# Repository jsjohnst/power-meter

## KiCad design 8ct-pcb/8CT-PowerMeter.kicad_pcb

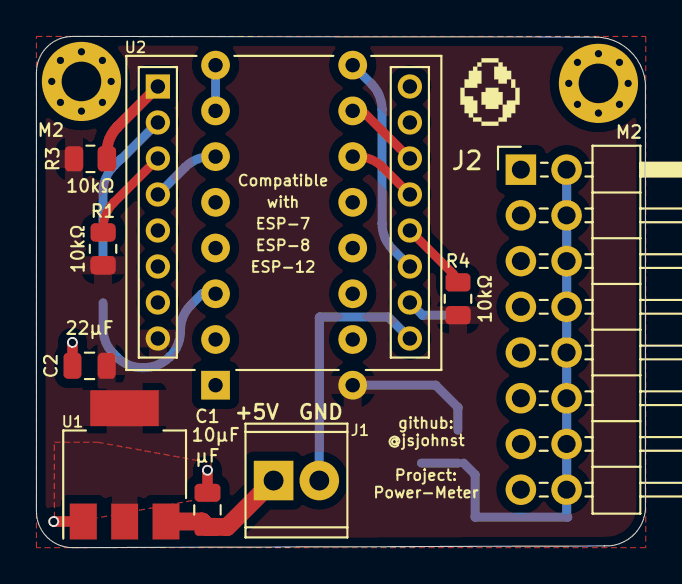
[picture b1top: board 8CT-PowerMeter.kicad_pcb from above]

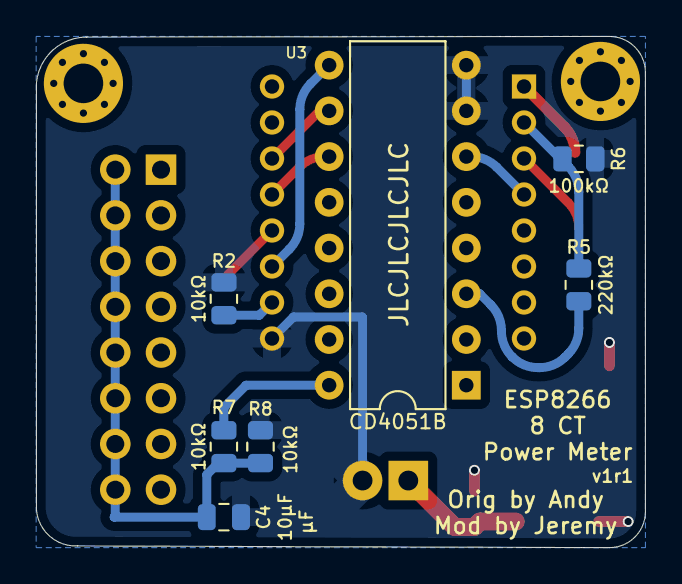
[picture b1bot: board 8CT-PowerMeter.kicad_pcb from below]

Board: 4 copper layers, 33.8 x 28.4 mm, 18 parts (7 on the bottom side), 22 nets.

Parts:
C1, C4: 10µF; C_0805_2012Metric
C2: 22µF; C_0805_2012Metric
H1, H2: M2; MountingHole_2.2mm_M2_Pad_Via
J1: Screw_Terminal_01x02; TerminalBlock_Phoenix_MPT-0,5-2-2.54_1x02_P2.54mm_Horizonta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
J2: Conn_02x08_Odd_Even; PinHeader_2x08_P2.54mm_Horizontal
R1, R2, R3, R4, R7, R8: 10kΩ; R_0805_2012Metric
R5: 220kΩ; R_0805_2012Metric
R6: 100kΩ; R_0805_2012Metric
U1: AMS1117-3.3; SOT-223-3_TabPin2
U2: ESP-07; ESP-12-Socket-Cutout
U3: CD4051B; DIP-16_W7.62mm

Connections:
+3V3: C2.1, R1.1, R3.1, R4.1, R7.1, U1.2 (VO), U2.8 (VCC), U3.16 (VDD)
/+5V: C1.1, J1.1, U1.3 (VI)
/ADCRAW: R5.1, U3.3 (X)
A0: R5.2, R6.1, U2.2 (ADC)
GND: C1.2, C2.2, C4.1, J1.2, R2.2, R6.2, R8.2, U1.1 (GND), U2.15 (GND), U3.7 (VEE), U3.8 (VSS)
GPIO2: U2.17 (GPIO2), U3.9 (C)
GPIO4: U2.19 (GPIO4), U3.11 (A)
GPIO5: U2.20 (GPIO5), U3.10 (B)
GPIO16: U2.4 (GPIO16), U3.6 (INH)
unnamed: C4.2, J2.2, J2.4, J2.6, J2.8, J2.10, J2.12, J2.14, J2.16, R7.2, R8.1
unnamed: R1.2, U2.3 (EN)
unnamed: R2.1, U2.16 (GPIO15)
unnamed: R3.2, U2.1 (~RST)
unnamed: R4.2, U2.18 (GPIO0)
PM1: J2.1, U3.13 (X0)
PM2: J2.3, U3.14 (X1)
PM3: J2.5, U3.15 (X2)
PM4: J2.7, U3.12 (X3)
PM5: J2.15, U3.1 (X4)
PM6: J2.9, U3.5 (X5)
PM7: J2.13, U3.2 (X6)
PM8: J2.11, U3.4 (X7)

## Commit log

2023-01-01 Adding new 8 channel version of Power Meter
    As the mux is 8 channels, why limit ourselves to just 3 CTs? :) To keep
    the small footprint of the original board design as close as possible,
    the board was increased from 2 layers to 4 layers. The signal lines
    going from the mux to the CT pin header uses the inner two layers of the
    board design.
    This new design passes KiCad validation checks, but has not been
